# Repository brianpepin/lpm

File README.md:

# LPM
LPM is a laser power meter used for reading the output power of a laser. It is designed to use a power sensor from Ophir, but any sensor that can produce a linear voltage related to power can be used.  It supplies +12 and -12 volt supplies to the sensor to power it, if needed.

## Features
* 24 bit ADC for precision
* Logging to onboard 64KB flash memory
* Logs viewable graphically and can be output to PC using built-on USB serial port
* Rechargeable battery through USB-C connector
* Software calibration can use any sensor

_(note - the Eagle files included in this repo do not need the jumper and resistor hacks you see here.  They've been fixed)_

### Calibration
The board must be calibrated before use.  This can be done through the menu.  Connect a stable voltage source to the sensor input (11.5 volts maximum) and enter the calibration menu.  This will display six digits (###.###), and represents the laser power level at that voltage for the sensor you plan to use.  Use the D-Pad to adjust the digits and click down to accept.

### Usage
Clicking down on the D-Pad turns the unit on. There is an automatic sleep of 10 minutes of inactivity.  Sleep is disabled during logging. Pressing right, left, select or on the D-Pad enters the menu. From here you can zero the max and averages, configure logging cadence or view the log if it exists.  There are also two short-cuts:  down zeros the max and averages and up starts / stops logging. Pressing and holding in the D-Pad for two seconds turns the unit off.

### Logging
When in logging view you can position the cursor using left and right to show the value at that location.  The log can be sent through USB -- the LPM shows up as a serial port, so you need your own software to pull the log data off.

## Case
I've also included the CAD files (IGES format) of a case that fits this.  I decided to make the sensor and display all part of the same unit so I can just throw it in my toolbox and not have to worry about a bunch of wires.

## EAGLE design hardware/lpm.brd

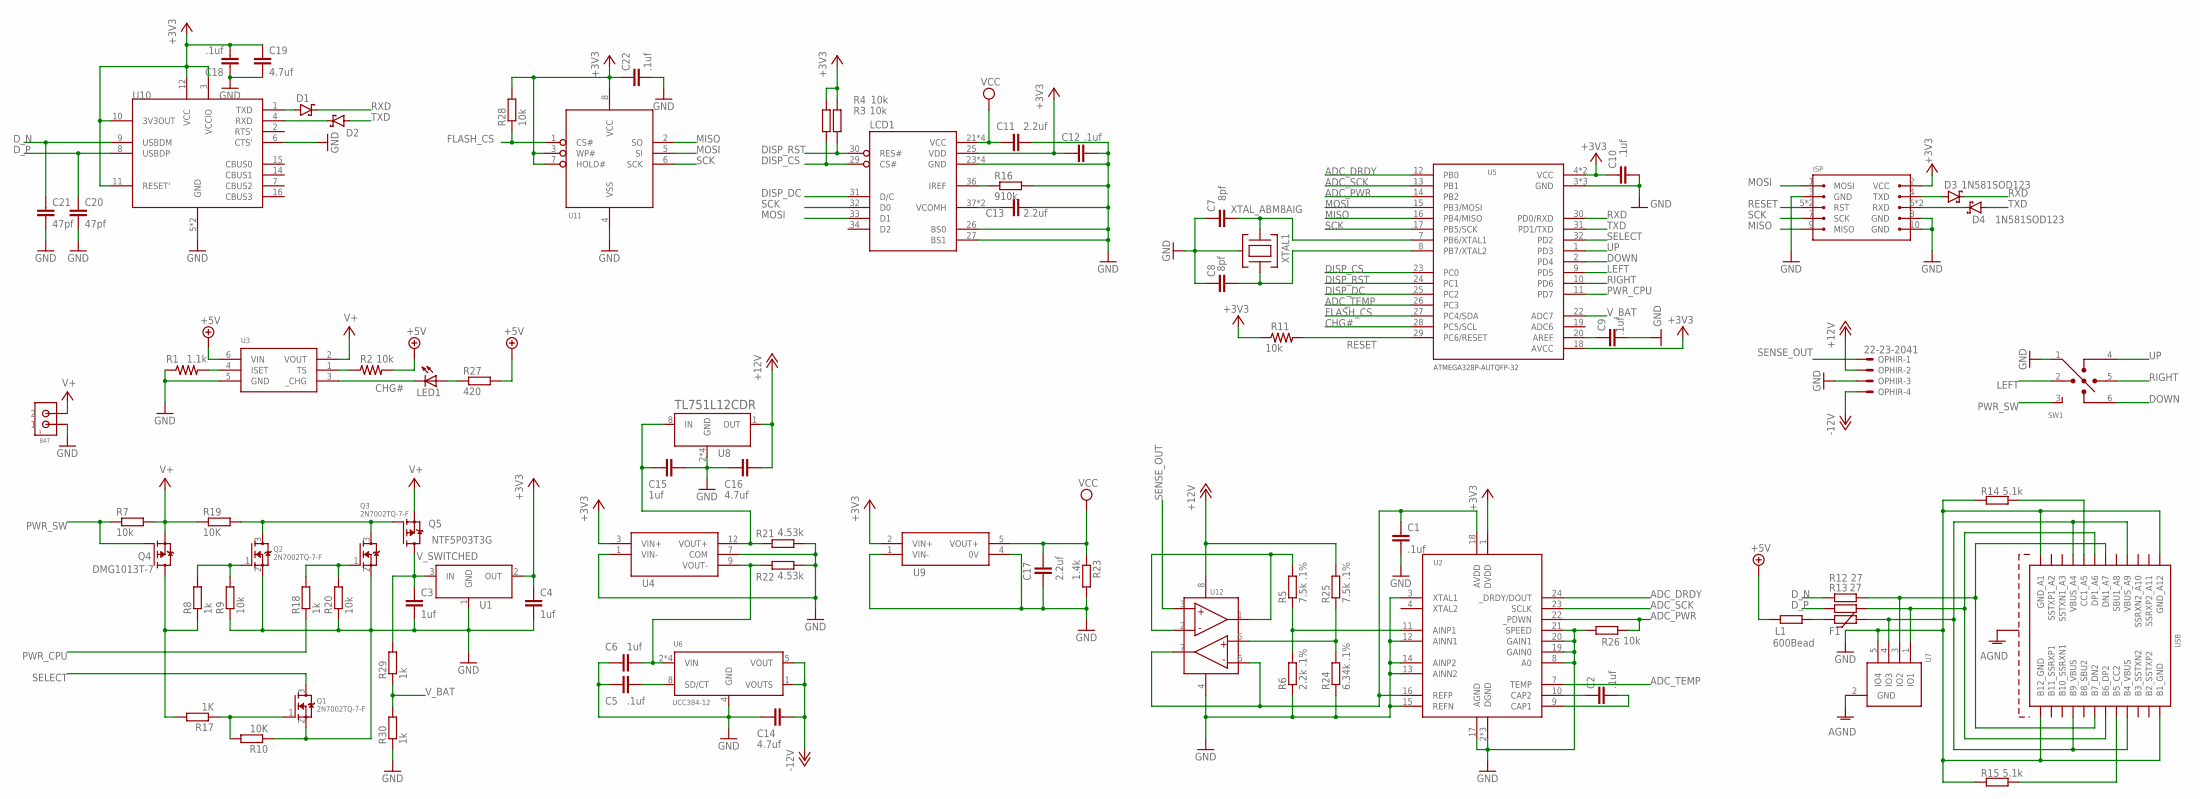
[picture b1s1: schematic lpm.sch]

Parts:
BAT: 2PIN_CONNJST_SH; JST-SM02B-SRSS-TB
C1, C2, C5, C9, C10, C12, C18, C22: .1uf; C0805
C3, C4, C6, C15: 1uf; C0805
C7, C8: 8pf; C0805
C11, C13, C17: 2.2uf; C0805
C14, C16, C19: 4.7uf; C0805
C20, C21: 47pf; C0805
D1, D2, D3, D4: 1N581SOD123; SOD3715X135
F1: MF-PSHT035KX-2; FUSC2113X120N
ISP: 10PIN_ISPTC2050; TC2050-IDC
L1: 600Bead; M0805
LCD1: EAOLEDL128-6
LED1: LEDCHIPLED_0805; CHIPLED_0805
OPHIR: 22-23-2041
Q1, Q2, Q3: 2N7002TQ-7-F; SOT50P160X80-3
Q4: DMG1013T-7; SOT50P160X80-3
Q5: NTF5P03T3G; SOT230P700X180-4
R1: 1.1k; R0805
R2, R3, R4, R7, R9, R11, R20, R26, R28: 10k; R0805
R5, R25: 7.5k .1%; R0805
R6: 2.2k .1%; R0805
R8, R18, R29, R30: 1k; R0805
R10, R19: 10K; R0805
R12, R13: 27; M0805
R14, R15: 5.1k; M0805
R16: 910k; R0805
R17: 1K; R0805
R21, R22: 4.53k; R0805
R23: 1.4k; R0805
R24: 6.34k .1%; R0805
R27: 420; R0805
SW1: JS-5208
U1: AZ1117E-3.3SOT-223; SOT230P700X180-4
U2: ADS1232; SOP65P640X120-24
U3: BQ21040SOT-23; SOT95P280X145-6
U4: NTA0315MC-R
U5: ATMEGA328P-AUTQFP-32; QFP80P887X887X120-32
U6: UCC384-12; SOIC127P599X175-8
U7: ESDS314; SOT95P282X145-5
U8: TL751L12CDR; SOIC127P599X175-8
U9: ISE0312A
U10: FT230XSSOP16; SOP63P599X175-16
U11: NV25640DWHFT3G; SOIC127P599X175-8
U12: OPA2210VSSOP8; SOP65P490X110-8
USB: USBC_FEMALEUJ31-CH-31-SMT-TR; USBC_UJ31-CH-31-SMT-TR
XTAL1: XTAL_ABM8AIG; XTAL_SMT_3.2X2.5

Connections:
+3V3: C4.1, C10.1, C12.1, C18.2, C19.1, C22.1, ISP.2 (VCC), LCD1.25 (VDD), R3.2, R4.2, R11.1, R28.2, U1.2 (OUT), U2.1 (DVDD), U4.3 (VIN+), U5.4 (VCC), U5.6 (VCC), U5.18 (AVCC), U9.2 (VIN+), U10.3 (VCCIO), U10.10 (3V3OUT), U10.11 (RESET'), U10.12 (VCC), U11.3 (WP#), U11.7 (HOLD#), U11.8 (VCC)
+5V: L1.1, R2.2, R27.2, U3.6 (VIN)
+12V: C16.2, OPHIR.2, R25.2, U8.1 (OUT), U12.8 (V+)
-12V: C14.2, OPHIR.4, U6.1 (VOUTS), U6.5 (VOUT)
ADC_DRDY: U2.24 (_DRDY/DOUT), U5.12 (PB0)
ADC_PWR: R26.2, U2.22 (_PDWN), U5.14 (PB2)
ADC_SCK: U2.23 (SCLK), U5.13 (PB1)
ADC_TEMP: U2.7 (TEMP), U5.26 (PC3)
AGND: U7.2 (GND), USB.SHLD@1 (SHLD), USB.SHLD@2 (SHLD), USB.SHLD@3 (SHLD), USB.SHLD@4 (SHLD), USB.SHLD@5 (SHLD), USB.SHLD@6 (SHLD), USB.SHLD@7 (SHLD), USB.SHLD@8 (SHLD)
CHG#: LED1.C, U3.3 (_CHG), U5.28 (PC5/SCL)
DISP_CS: LCD1.29 (CS#), R4.1, U5.23 (PC0)
DISP_DC: LCD1.31 (D/C), U5.25 (PC2)
DISP_RST: LCD1.30 (RES#), R3.1, U5.24 (PC1)
DOWN: SW1.6 (D), U5.2 (PD4)
D_N: C21.1, R12.1, U10.9 (USBDM)
D_P: C20.1, R13.1, U10.8 (USBDP)
FLASH_CS: R28.1, U5.27 (PC4/SDA), U11.1 (CS#)
GND: BAT.1, C1.2, C3.2, C4.2, C5.1, C6.1, C7.1, C8.1, C9.2, C10.2, C11.2, C12.2, C13.2, C14.1, C15.2, C16.1, C17.2, C18.1, C19.2, C20.2, C21.2, C22.2, ISP.3 (GND), ISP.8 (GND), ISP.10 (GND), LCD1.23 (GND), LCD1.24 (GND), LCD1.26 (BS0), LCD1.27 (BS1), LCD1.28 (GND), LCD1.35 (GND), OPHIR.3, Q1.2 (S), Q2.2 (S), Q3.2 (S), R1.1, R6.1, R9.1, R10.1, R14.1, R15.1, R16.2, R20.1, R21.2, R22.2, R23.2, R24.1, R26.1, R30.1, SW1.1 (C), U1.1 (GND), U2.2 (DGND), U2.3 (XTAL1), U2.5 (DGND), U2.6 (DGND), U2.8 (A0), U2.12 (AINN1), U2.13 (AINN2), U2.14 (AINP2), U2.15 (REFN), U2.17 (AGND), U2.19 (GAIN0), U2.20 (GAIN1), U2.21 (SPEED), U3.5 (GND), U4.1 (VIN-), U4.7 (COM), U5.3 (GND), U5.5 (GND), U5.21 (GND), U6.4 (GND), U7.5 (IO4), U8.2 (GND), U8.3 (GND), U8.6 (GND), U8.7 (GND), U9.1 (VIN-), U9.4 (0V), U10.5 (GND), U10.6 (CTS'), U10.13 (GND), U11.4 (VSS), U12.4 (V-), USB.A1 (GND_A1), USB.A12 (GND_A12), USB.B1 (B1_GND), USB.B12 (B12_GND), XTAL1.2 (CASE), XTAL1.4 (CASE)
LEFT: SW1.2 (L), U5.9 (PD5)
MISO: ISP.9 (MISO), U5.16 (PB4/MISO), U11.2 (SO)
MOSI: ISP.1 (MOSI), LCD1.33 (D1), U5.15 (PB3/MOSI), U11.5 (SI)
unnamed: R1.2, U3.4 (ISET)
unnamed: Q4.3 (D), R8.1, R17.2
unnamed: R2.1, U3.1 (TS)
unnamed: LED1.A, R27.1
unnamed: Q2.1 (G), R8.2, R9.2
unnamed: Q2.3 (D), Q3.3 (D), Q5.1 (G), R19.2
unnamed: R5.1, R6.2, U2.11 (AINP1)
unnamed: C7.2, U5.7 (PB6/XTAL1), XTAL1.1
unnamed: Q3.1 (G), R18.2, R20.2
unnamed: C8.2, U5.8 (PB7/XTAL2), XTAL1.3
unnamed: C9.1, U5.20 (AREF)
unnamed: R14.2, USB.A5 (CC1_A5)
unnamed: R15.2, USB.B5 (B5_CC2)
unnamed: F1.1, L1.2
unnamed: Q1.1 (G), R10.2, R17.1
unnamed: LCD1.36 (IREF), R16.1
unnamed: C13.1, LCD1.37 (VCOMH), LCD1.38 (VCOMH)
unnamed: R24.2, R25.1, U12.5 (IN2+)
unnamed: D3.A, ISP.4 (TXD)
unnamed: D4.C, ISP.6 (RXD), ISP.L6 (RXD)
unnamed: D1.A, U10.1 (TXD)
unnamed: C5.2, U6.8 (SD/CT)
unnamed: C6.2, R22.1, U4.9 (VOUT-), U6.2 (VIN), U6.3 (VIN), U6.6 (VIN), U6.7 (VIN)
unnamed: C15.1, R21.1, U4.12 (VOUT+), U8.8 (IN)
unnamed: D2.C, U10.4 (RXD)
unnamed: R5.2, U12.1 (OUT1), U12.2 (IN1-)
unnamed: C1.1, U2.16 (REFP), U2.18 (AVDD), U12.6 (IN2-), U12.7 (OUT2)
unnamed: R12.2, U7.3 (IO2), USB.A7 (DN1_A7), USB.B7 (B7_DN2)
unnamed: R13.2, U7.1 (IO1), USB.A6 (DP1_A6), USB.B6 (B6_DP2)
unnamed: F1.2, U7.4 (IO3), USB.A4 (VBUS_A4), USB.A9 (VBUS_A9), USB.B4 (B4_VBUS), USB.B9 (B9_VBUS)
unnamed: C2.1, U2.10 (CAP2)
unnamed: C2.2, U2.9 (CAP1)
PWR_CPU: R18.1, U5.11 (PD7)
PWR_SW: Q4.1 (G), R7.1, SW1.3
RESET: ISP.5 (RST), ISP.L5 (RST), R11.2, U5.29 (PC6/RESET)
RIGHT: SW1.5 (R), U5.10 (PD6)
RXD: D1.C, D3.C, U5.30 (PD0/RXD)
SCK: ISP.7 (SCK), LCD1.32 (D0), U5.17 (PB5/SCK), U11.6 (SCK)
SELECT: Q1.3 (D), U5.32 (PD2)
SENSE_OUT: OPHIR.1, U12.3 (IN1+)
TXD: D2.A, D4.A, U5.31 (PD1/TXD)
UP: SW1.4 (U), U5.1 (PD3)
V+: BAT.2, Q4.2 (S), Q5.3 (S), R7.2, R19.1, U3.2 (VOUT)
VCC: C11.1, C17.1, LCD1.21 (VCC), LCD1.22 (VCC), LCD1.39 (VCC), LCD1.40 (VCC), R23.1, U9.5 (VOUT+)
V_BAT: R29.1, R30.2, U5.22 (ADC7)
V_SWITCHED: C3.1, Q5.2 (D), Q5.4 (D), R29.2, U1.3 (IN)

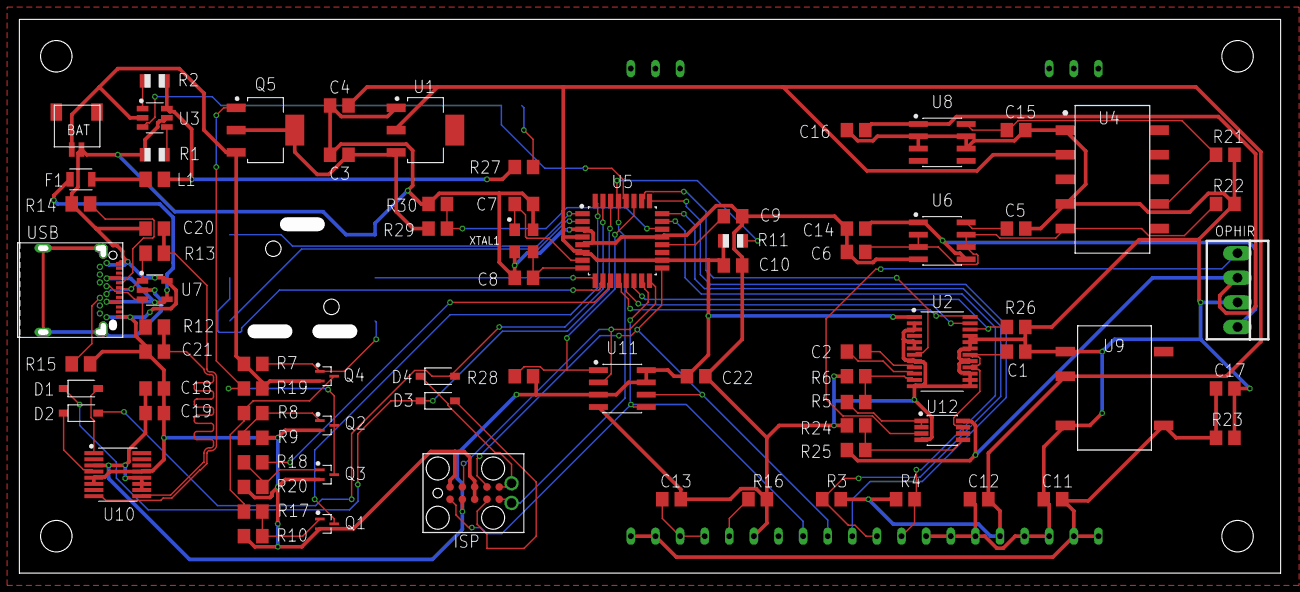
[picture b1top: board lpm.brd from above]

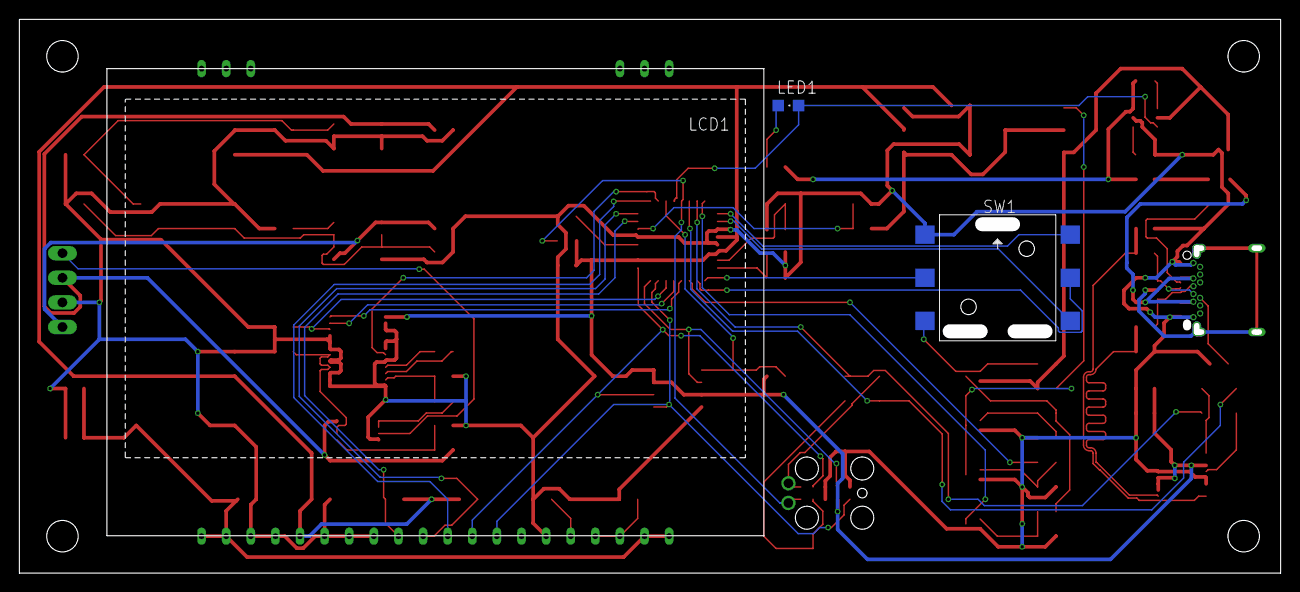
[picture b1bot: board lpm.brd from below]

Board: 2 copper layers, 130.2 x 57.1 mm, 83 parts (3 on the bottom side), 67 nets.

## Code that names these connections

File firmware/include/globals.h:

#pragma once

#include <Arduino.h>
#include <SPI.h>
#include <avr/pgmspace.h>

//
// Display port map
//

// DISP_CS:    PC0 pin A0
// DISP_RST:   PC1 pin A1 
// DISP_DC:    PC2 pin A2

#define PIN_DISPLAY_CS    A0
#define PIN_DISPLAY_RST   A1
#define PIN_DISPLAY_DC    A2

//
// AD port map
//

// ADC_DRDY     PB0 pin 8
// ADC_SCK      PB1 pin 9
// ADC_PWR      PB2 pin 10
// ADC_TEMP     PC3 pin A3

#define PIN_ADC_DRDY 8
#define PIN_ADC_SCK  9
#define PIN_ADC_PWR  10
#define PIN_ADC_TEMP A3

//
// D-Pad port map
//

// PWR_CPU      PD7 pin 7
// RIGHT        PD6 pin 6
// LEFT         PD5 pin 5
// DOWN         PD4 pin 4
// UP           PD3 pin 3
// SELECT       PD2 pin 2

#define PIN_PWR_CPU 7
#define PIN_RIGHT   6
#define PIN_LEFT    5
#define PIN_DOWN    4
#define PIN_UP      3
#define PIN_SELECT  2

//
// Battery status port map
//

// CHG      PC5     A5
// V_BAT    ADC7    A7

#define PIN_CHG     A5
#define PIN_V_BAT   A7

//
// Flash Memory port map
//

// FLASH_CS PC4 A4

#define PIN_FLASH_CS A4

// Macros

 #define COUNT_OF(a) (sizeof(a) / sizeof(*a))

// FONTS
#define MENU_HEADER_FONT        u8g2_font_profont11_tr
#define MENU_ITEM_FONT          u8g2_font_profont11_tr
#define MENU_ARROW_FONT         u8g2_font_open_iconic_arrow_1x_t
#define NUMBER_SELECTOR_FONT    u8g2_font_profont17_tn
#define NOTICE_FONT             u8g2_font_haxrcorp4089_tr
#define MAIN_READING_FONT       u8g2_font_profont29_tn
#define MAIN_READING_FONT_SM    u8g2_font_profont22_tn
#define MAIN_UNITS_FONT         u8g2_font_tenthinnerguys_tr
#define GRAPH_READING_FONT      u8g2_font_blipfest_07_tr
#define LOGGING_INDICATOR_FONT  u8g2_font_blipfest_07_tr

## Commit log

2020-04-05 Rightside up?
2020-04-06 Added how to turn it off....
